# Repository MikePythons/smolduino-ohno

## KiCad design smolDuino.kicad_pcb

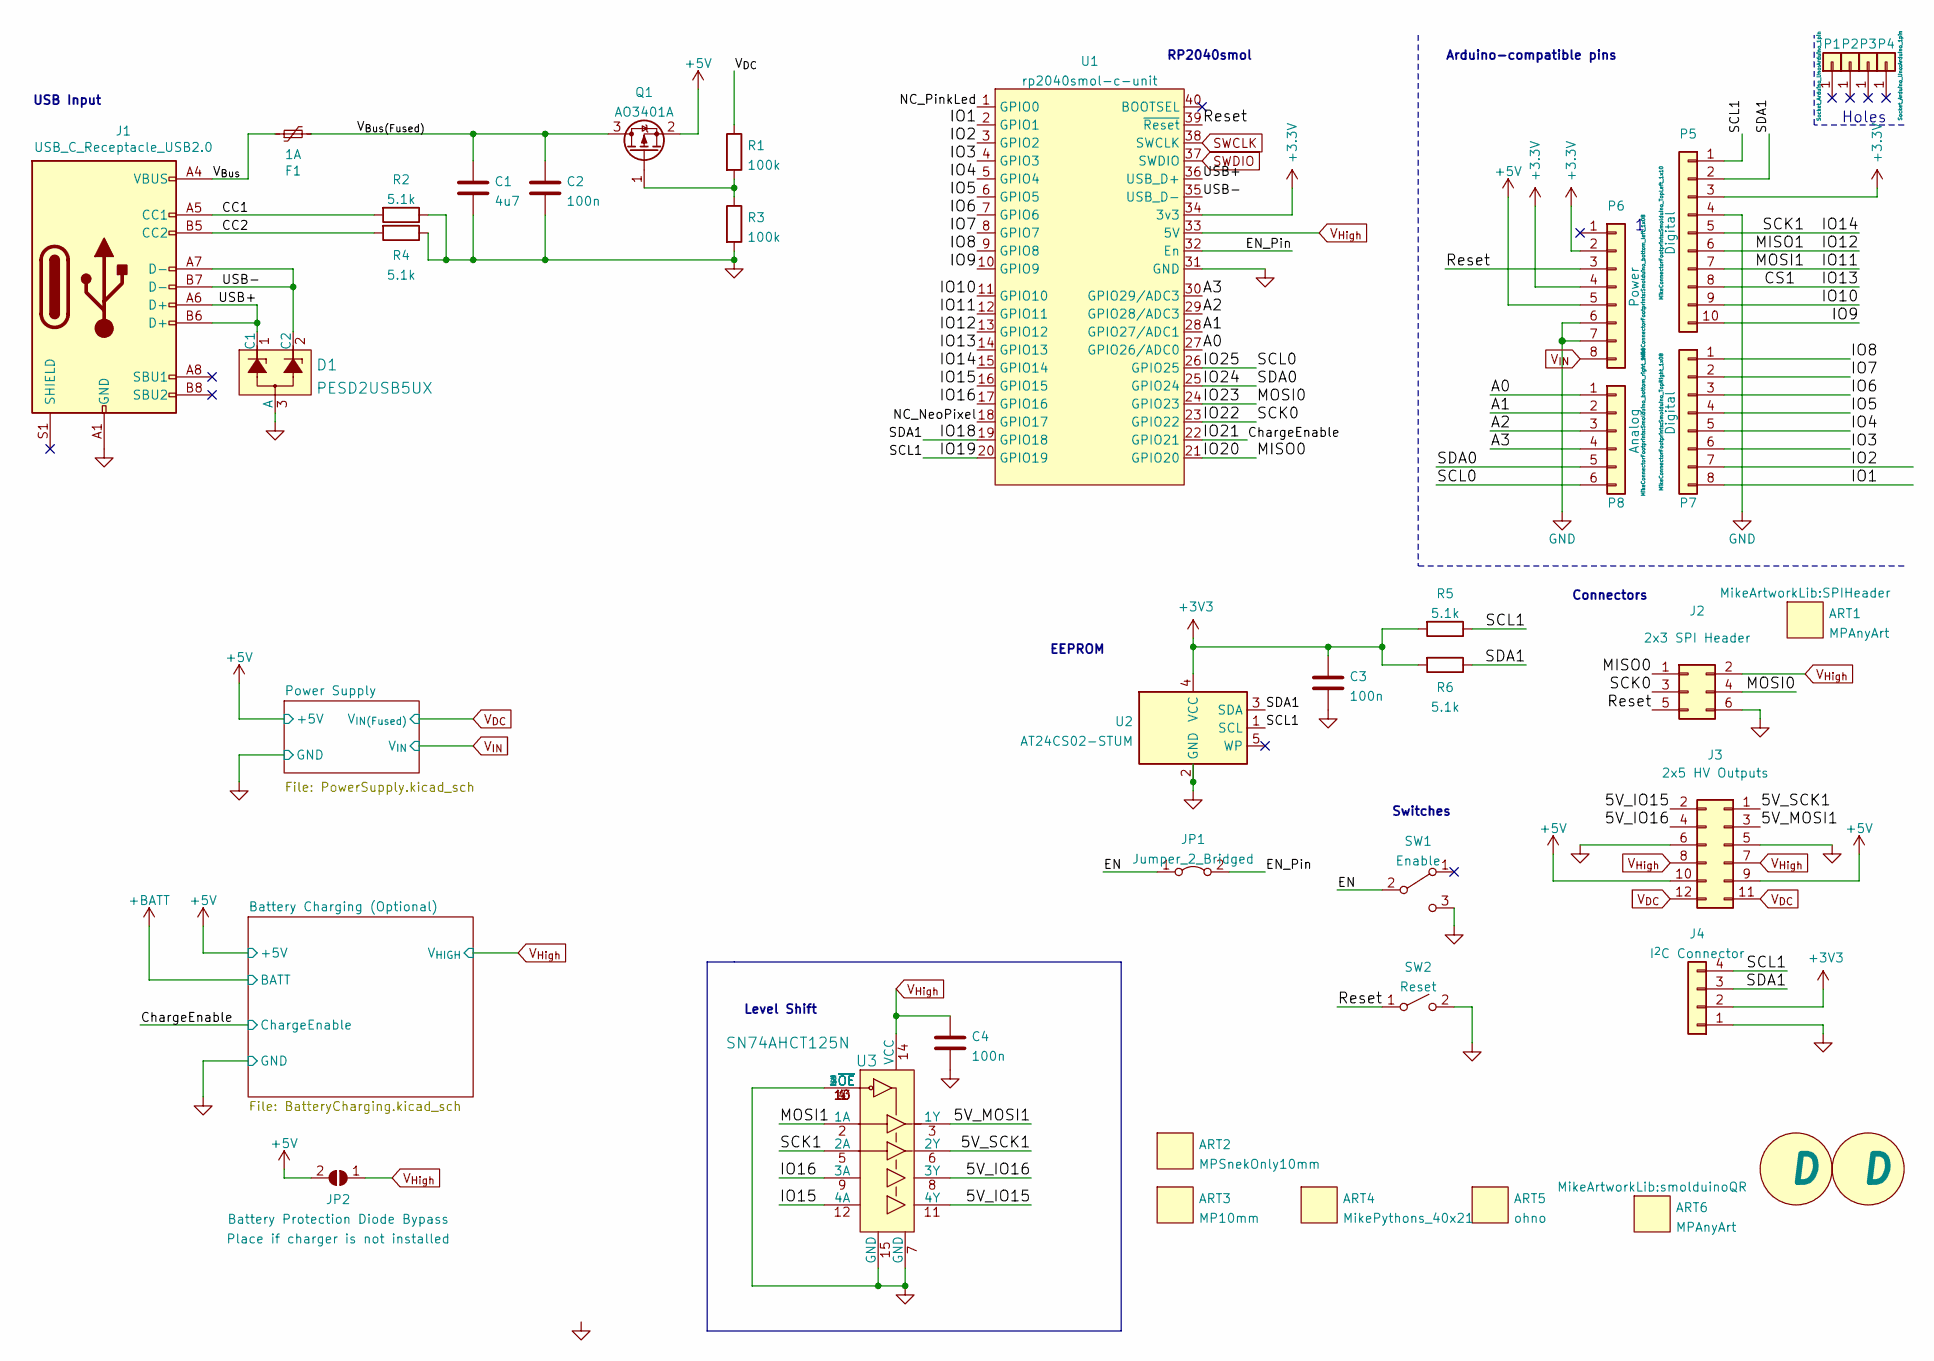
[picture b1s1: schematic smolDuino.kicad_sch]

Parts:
ART1: MPAnyArt; SPIHeader
ART2: MPSnekOnly10mm; MPSnekOnly_10x6mm
ART3: MP10mm; MPSquare_10mm
ART4: MikePythons_40x21; MikePythons_22x12
ART5: ohno
ART6: MPAnyArt; smolduinoQR
C1: 4u7; C_0805_2012Metric
C2, C3, C4: 100n; C_0603_1608Metric
D1: PESD2USB5UX; SOT-23-3
F1: 1A; Fuse_1206_3216Metric
J1: USB_C_Receptacle_USB2.0; USB_C_Receptacle_Palconn_UTC16-G
J2: 2x3 SPI Header; PinHeader_2x03_P2.54mm_Vertical
J3: 2x5 HV Outputs; PinSocket_2x06_P2.54mm_Vertical
J4: I^{2}C Connector; JST_SH_SM04B-SRSS-TB_1x04-1MP_P1.00mm_Horizontal
JP1: Jumper_2_Bridged; SolderJumper-2_P1.3mm_Bridged_Pad1.0x1.5mm
JP2: Battery Protection Diode Bypass; SolderJumper-2_P1.3mm_Open_TrianglePad1.0x1.5mm
MISC1, MISC2: D; RevisionSymbol
P1, P2, P3, P4: CONN_01X01; Arduino_1pin
P5: Digital; Smolduino_TopLeft_1x10
P6: Power; Smolduino_bottom_left_1x08
P7: Digital; Smolduino_TopRight_1x08
P8: Analog; Smolduino_bottom_right_1x06
Q1: AO3401A; SOT-23
R1, R3: 100k; R_0603_1608Metric
R2, R4, R5, R6: 5.1k; R_0603_1608Metric
SW1: Enable; SW_SPDT_PCM12
SW2: Reset; E-Switch-TL3330AF260QG-MFG
U1: rp2040smol-c-unit; THT_4x10_smol_dual
U2: AT24CS02-STUM; SOT-23-5
U3: SN74AHCT125N; Texas_S-PVQFN-N14; MPN SN74AHCT125N; Digi-Key_PN 296-4655-5-ND

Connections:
+5V: J3.9, J3.10, JP2.2 (B), P6.5, Q1.2 (S); also elsewhere on the board
/5V_IO15: J3.2, U3.11 (4Y)
/5V_IO16: J3.4, U3.8 (3Y)
/5V_MOSI1: J3.3, U3.3 (1Y)
/5V_SCK1: J3.1, U3.6 (2Y)
/A0: P8.1, U1.27 (GPIO26/ADC0)
/A1: P8.2, U1.28 (GPIO27/ADC1)
/A2: P8.3, U1.29 (GPIO28/ADC3)
/A3: P8.4, U1.30 (GPIO29/ADC3)
/CC1: J1.A5 (CC1), R2.2
/CC2: J1.B5 (CC2), R4.2
/CS1: P5.8, U1.14 (GPIO13)
/ChargeEnable: U1.22 (GPIO21); also elsewhere on the board
/EN: JP1.1 (A), SW1.2 (B)
/EN_Pin: JP1.2 (B), U1.32 (En)
/IO1: P7.8, U1.2 (GPIO1)
/IO2: P7.7, U1.3 (GPIO2)
/IO3: P7.6, U1.4 (GPIO3)
/IO4: P7.5, U1.5 (GPIO4)
/IO5: P7.4, U1.6 (GPIO5)
/IO6: P7.3, U1.7 (GPIO6)
/IO7: P7.2, U1.8 (GPIO7)
/IO8: P7.1, U1.9 (GPIO8)
/IO9: P5.10, U1.10 (GPIO9)
/IO10: P5.9, U1.11 (GPIO10)
/IO11: P5.7, U1.12 (GPIO11), U3.2 (1A)
/IO12: P5.6, U1.13 (GPIO12)
/IO14: P5.5, U1.15 (GPIO14), U3.5 (2A)
/IO15: U1.16 (GPIO15), U3.12 (4A)
/IO16: U1.17 (GPIO16), U3.9 (3A)
/IO18: J4.3, P5.2, R6.1, U1.19 (GPIO18), U2.3 (SDA)
/IO19: J4.4, P5.1, R5.1, U1.20 (GPIO19), U2.1 (SCL)
/IO20: J2.1, U1.21 (GPIO20)
/IO22: J2.3, U1.23 (GPIO22)
/IO23: J2.4, U1.24 (GPIO23)
/IO24: P8.5, U1.25 (GPIO24)
/IO25: P8.6, U1.26 (GPIO25)
/NC_NeoPixel: U1.18 (GPIO17)
/NC_PinkLed: U1.1 (GPIO0)
/Reset: J2.5, P6.3, SW2.1 (A), U1.39 (~Reset)
/USB+: D1.1 (C1), J1.A6 (D+), J1.B6 (D+), U1.36 (USB_D+)
/USB-: D1.2 (C2), J1.A7 (D-), J1.B7 (D-), U1.35 (USB_D-)
/V_{Bus}: F1.1, J1.A4 (VBUS), J1.A9 (VBUS), J1.B4 (VBUS), J1.B9 (VBUS)
/V_{Bus}_{(Fused)}: C1.2, C2.1, F1.2, Q1.3 (D)
GND: C1.1, C2.2, C3.2, C4.2, D1.3 (A), J1.A1 (GND), J1.A12 (GND), J1.B1 (GND), J1.B12 (GND), J2.6, J3.5, J3.6, J4.1, P5.4, P6.6, P6.7, R2.1, R3.2, R4.1, SW1.3 (C), SW2.2 (B), U1.31 (GND), U2.2 (GND), U3.1 (1~OE), U3.4 (2~OE), U3.7 (GND), U3.10 (3~OE), U3.13 (4~OE), U3.15 (GND); also elsewhere on the board
unnamed: Q1.1 (G), R1.2, R3.1
SWCLK: U1.38 (SWCLK)
SWDIO: U1.37 (SWDIO)
V_{DC}: J3.11, J3.12, R1.1; also elsewhere on the board
V_{High}: C4.1, J2.2, J3.7, J3.8, JP2.1 (A), U1.33 (5V), U3.14 (VCC); also elsewhere on the board
V_{IN}: P6.8; also elsewhere on the board

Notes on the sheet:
Connectors
Switches
Holes
EEPROM
RP2040smol
Level Shift
Arduino-compatible pins
USB Input

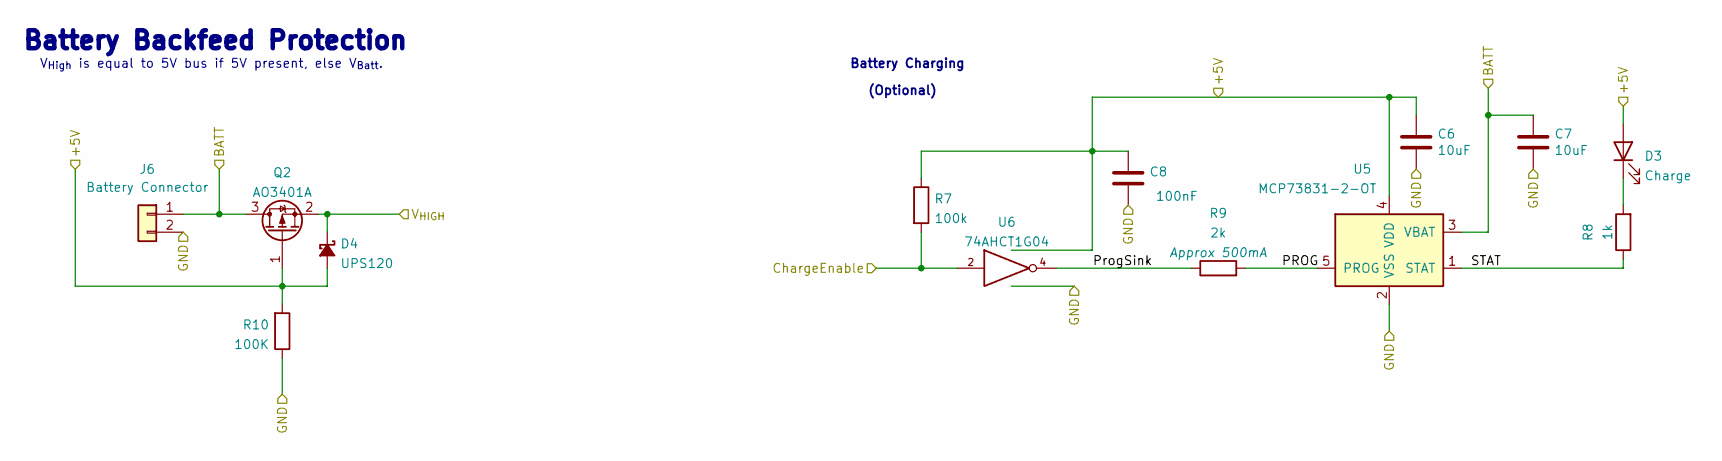
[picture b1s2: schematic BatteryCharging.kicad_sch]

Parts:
C6, C7: 10uF; C_0805_2012Metric
C8: 100nF; C_0603_1608Metric
D3: Charge; LED_0603_1608Metric
D4: UPS120; UPS120_D_Powermite_AK
J6: Battery Connector; JST_PH_S2B-PH-SM4-TB_1x02-1MP_P2.00mm_Horizontal
Q2: AO3401A; SOT-23
R7: 100k; R_0603_1608Metric
R8: 1k; R_0603_1608Metric
R9: 2k; R_0603_1608Metric
R10: 100K; R_0603_1608Metric
U5: MCP73831-2-OT; SOT-23-5
U6: 74AHCT1G04; SOT-353_SC-70-5

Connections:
+5V: C6.1, C8.1, D3.2 (A), D4.2 (A), Q2.1 (G), R7.1, R10.2, U5.4 (VDD), U6.5 (VCC); also elsewhere on the board
+BATT: C7.1, J6.1, Q2.3 (D), U5.3 (VBAT)
/Battery Charging (Optional)/PROG: R9.2, U5.5 (PROG)
/Battery Charging (Optional)/ProgSink: R9.1, U6.4
/Battery Charging (Optional)/STAT: R8.1, U5.1 (STAT)
/ChargeEnable: R7.2, U6.2; also elsewhere on the board
GND: C6.2, C7.2, C8.2, J6.2, R10.1, U5.2 (VSS), U6.3 (GND); also elsewhere on the board
unnamed: D3.1 (K), R8.2
V_{High}: D4.1 (K), Q2.2 (S); also elsewhere on the board

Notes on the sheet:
Battery Charging
V_{High} is equal to 5V bus if 5V present, else V_{Batt}.
(Optional)
Battery Backfeed Protection

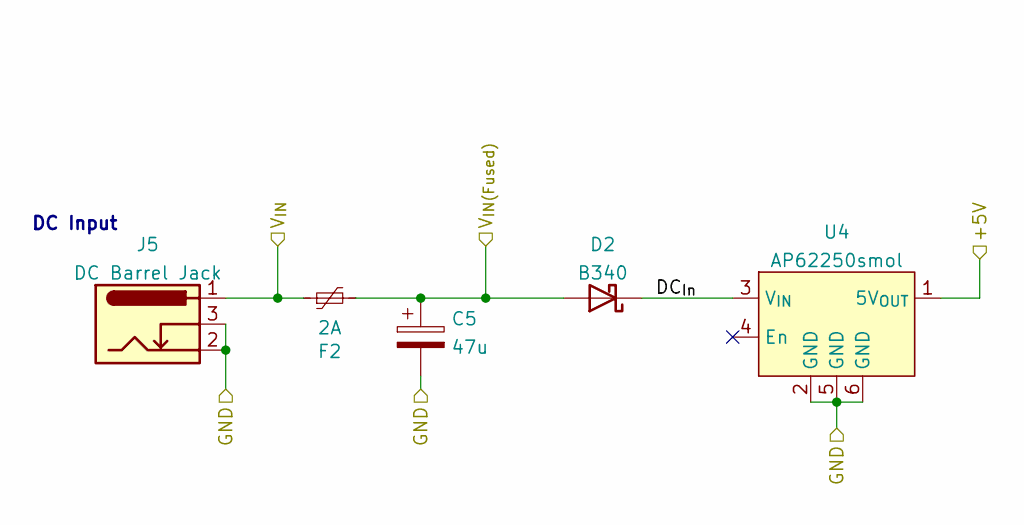
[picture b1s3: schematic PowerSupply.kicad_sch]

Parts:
C5: 47u; CP_Elec_6.3x5.4
D2: B340; D_SMC
F2: 2A; Fuse_2920_7451Metric
J5: DC Barrel Jack; BarrelJack_GCT_DCJ200-10-A_Horizontal
U4: AP62250smol; AP62250smol_C

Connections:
+5V: U4.1 (5V_{OUT}); also elsewhere on the board
/Power Supply/DC_{In}: D2.1 (K), U4.3 (V_{IN})
GND: C5.2, J5.2, J5.3, U4.2 (GND), U4.5 (GND), U4.6 (GND); also elsewhere on the board
V_{DC}: C5.1, D2.2 (A), F2.2; also elsewhere on the board
V_{IN}: F2.1, J5.1; also elsewhere on the board

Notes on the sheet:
DC Input

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
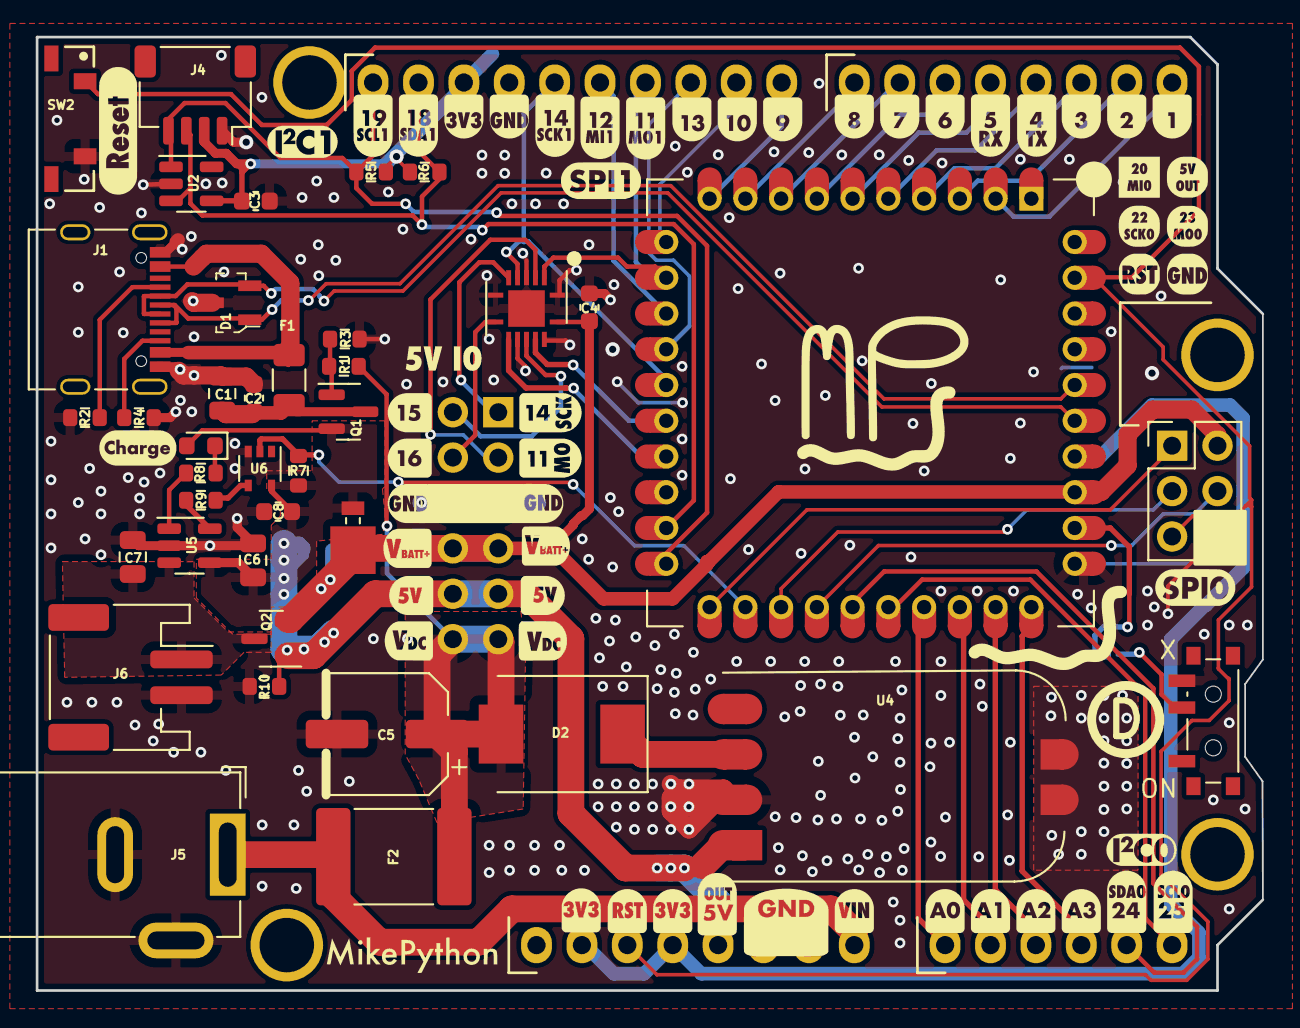
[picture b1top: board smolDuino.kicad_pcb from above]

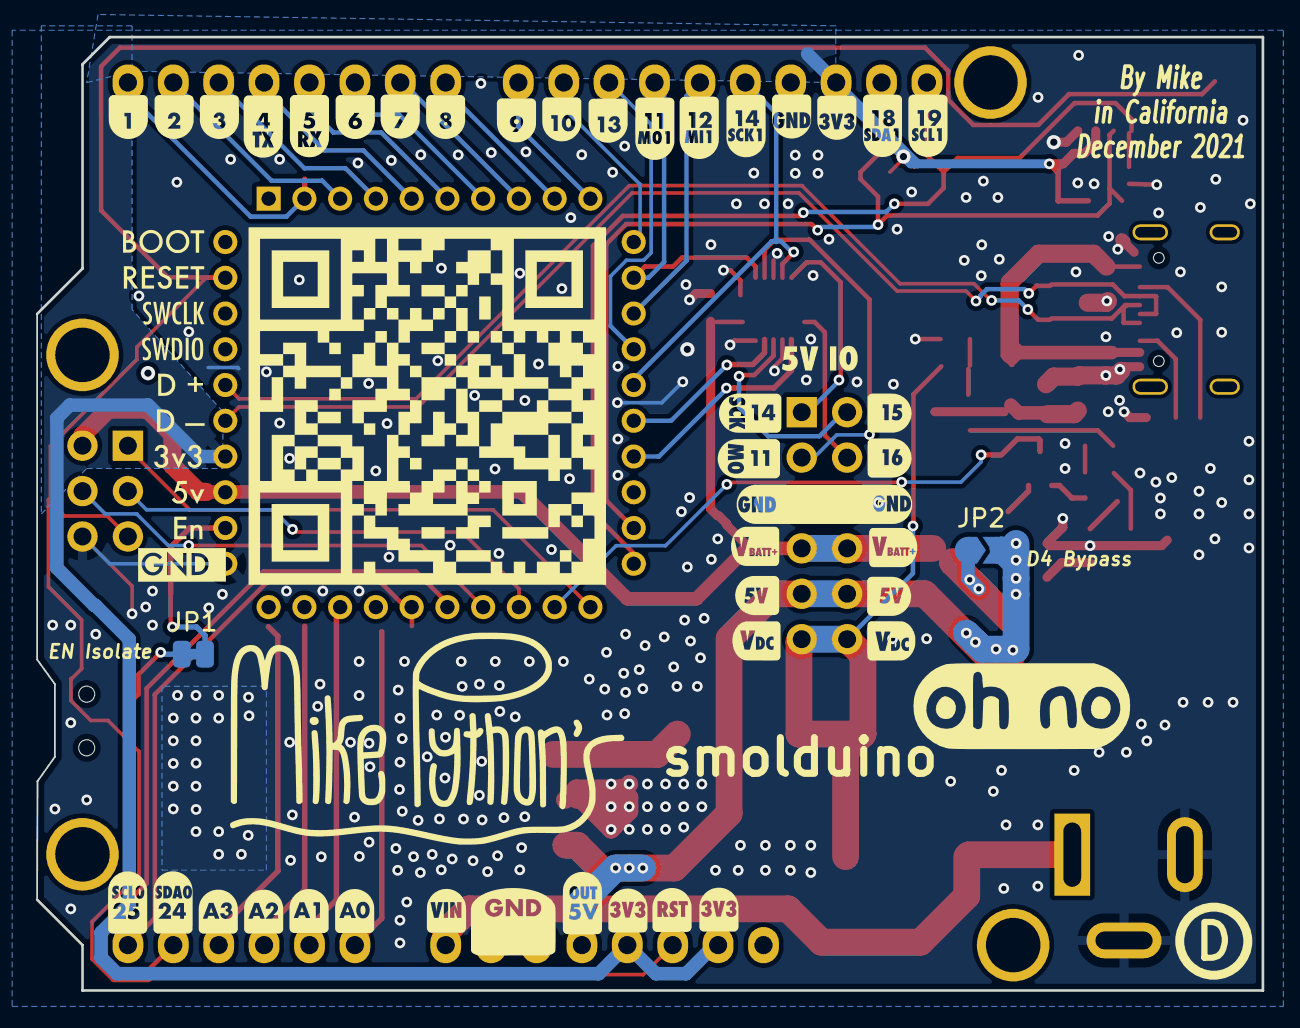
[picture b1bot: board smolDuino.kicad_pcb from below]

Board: 2 copper layers, 68.6 x 53.3 mm, 58 parts (6 on the bottom side), 54 nets.

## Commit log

2021-12-25 Initial upload; Rev C in progress and almost ready.
2021-12-25 commit before I ruin too much
2021-12-26 Removed the extra stuff i added
2021-12-29 Progress
2021-12-30 More progress. Charjsmol is removed and integrated directly onto the board.
2021-12-30 Rev C, I think
2021-12-30 Removed Charjsmol and integrated the charge circuit directly onto the board. Other than the BGA gas gauge IC (which could be deleted without a huge loss) there's no real reason to put the charger on 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
2021-12-30 Adding gerbers
2022-01-14 Remove Gas Gauge IC
